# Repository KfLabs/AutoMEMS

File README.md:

MotionProcessing
================

Code for motion sensors

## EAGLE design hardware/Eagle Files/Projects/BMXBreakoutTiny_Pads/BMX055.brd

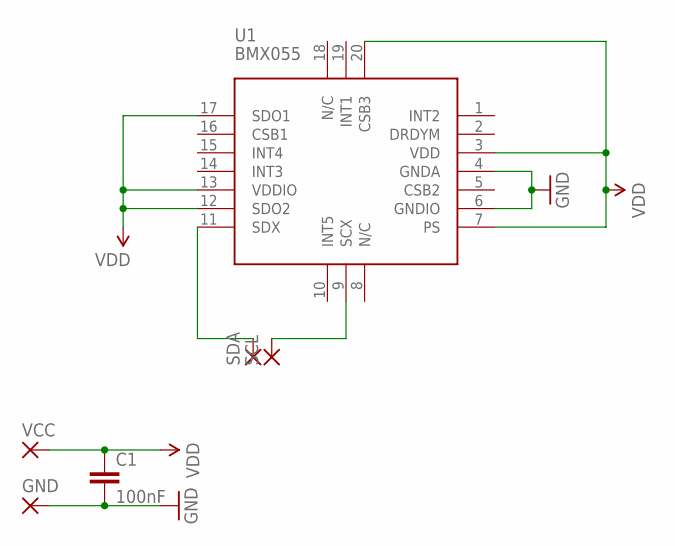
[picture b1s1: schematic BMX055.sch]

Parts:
C1: 100nF; 1206
GND: SMD2; SMD1,27-2,54
SCL: SMD2; SMD1,27-2,54
SDA: SMD2; SMD1,27-2,54
U1: BMX055
VCC: SMD2; SMD1,27-2,54

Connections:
GND: C1.2, GND.1, U1.4 (GNDA), U1.6 (GNDIO)
unnamed: SCL.1, U1.9 (SCX)
unnamed: SDA.1, U1.11 (SDX)
VDD: C1.1, U1.3 (VDD), U1.7 (PS), U1.12 (SDO2), U1.13 (VDDIO), U1.17 (SDO1), U1.20 (CSB3), VCC.1

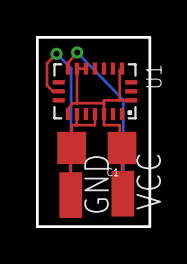
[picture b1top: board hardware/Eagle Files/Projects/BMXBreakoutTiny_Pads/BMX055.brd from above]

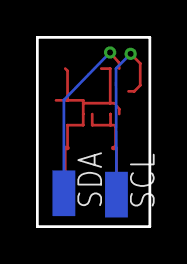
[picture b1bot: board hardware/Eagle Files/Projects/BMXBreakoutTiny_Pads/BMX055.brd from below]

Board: 2 copper layers, 6.2 x 10.5 mm, 6 parts (2 on the bottom side), 4 nets.

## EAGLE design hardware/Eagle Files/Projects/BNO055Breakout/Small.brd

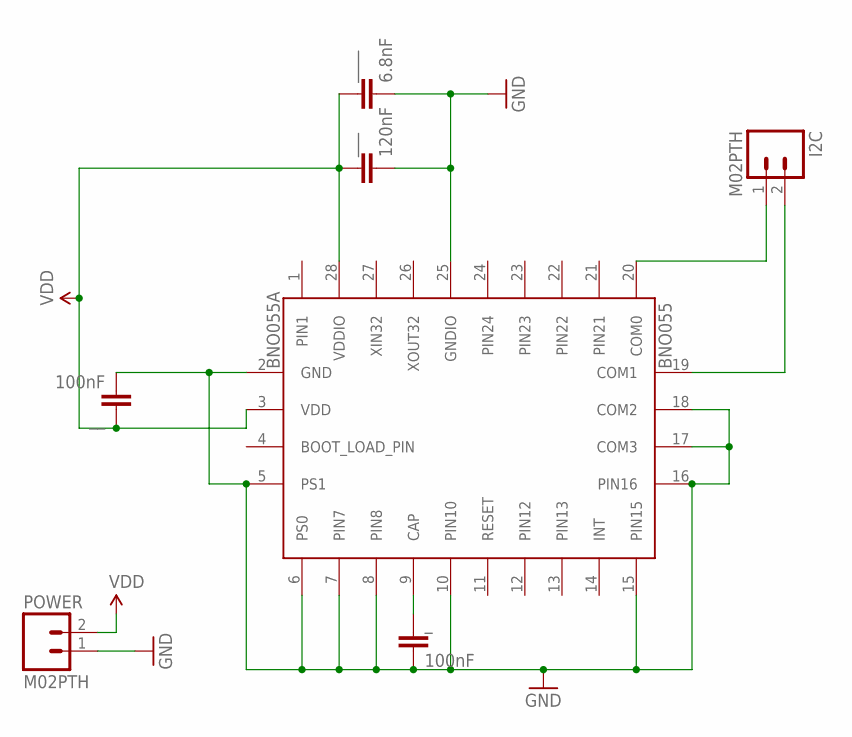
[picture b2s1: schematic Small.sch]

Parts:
BNO055: BNO055A; BNO055
I2C: M02PTH; 1X02
POWER: M02PTH; 1X02
_: 100nF; 1206
__: 100nF; 1206
___: 120nF; 1206
____: 6.8nF; 1206

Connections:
GND: BNO055.2 (GND), BNO055.5 (PS1), BNO055.6 (PS0), BNO055.7 (PIN7), BNO055.8 (PIN8), BNO055.10 (PIN10), BNO055.15 (PIN15), BNO055.16 (PIN16), BNO055.17 (COM3), BNO055.18 (COM2), BNO055.25 (GNDIO), POWER.1, _.2, __.2, ___.2, ____.2
unnamed: BNO055.9 (CAP), _.1
SCL: BNO055.19 (COM1), I2C.2
SDA: BNO055.20 (COM0), I2C.1
VDD: BNO055.3 (VDD), BNO055.28 (VDDIO), POWER.2, __.1, ___.1, ____.1

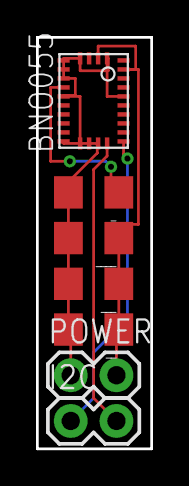
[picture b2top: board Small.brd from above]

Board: 2 copper layers, 6.3 x 22.9 mm, 7 parts (0 on the bottom side), 5 nets.

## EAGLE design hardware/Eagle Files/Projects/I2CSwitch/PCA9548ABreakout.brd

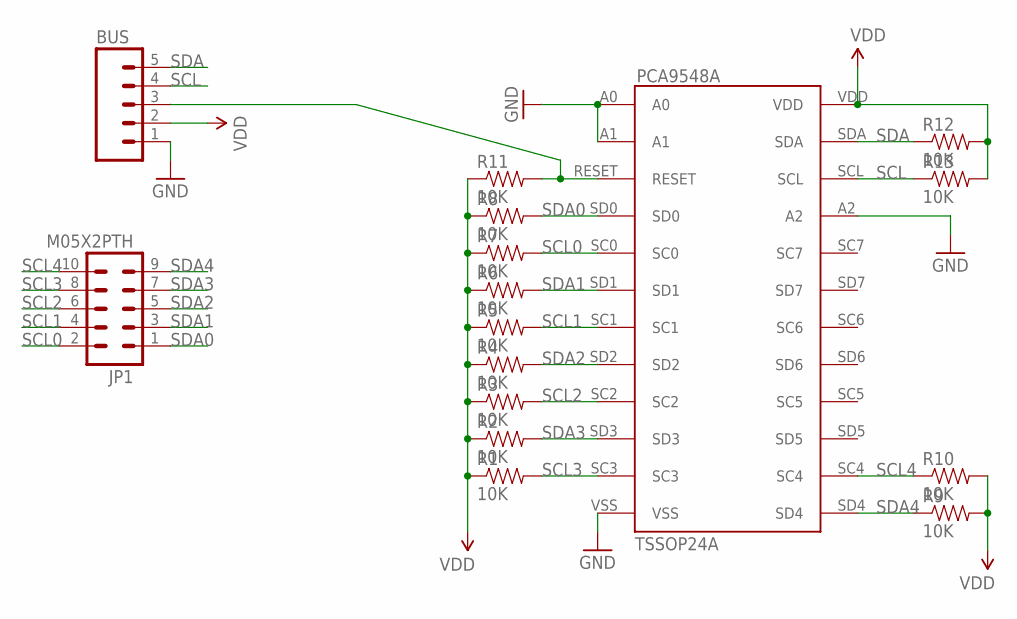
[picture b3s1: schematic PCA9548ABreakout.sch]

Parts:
BUS: M05PTH; 1X05
JP1: M05X2PTH; AVR_ICSP
PCA9548A: TSSOP24A; TSSOP24
R1, R2, R3, R4, R5, R6, R7, R8, R9, R10, R11, R12, R13: 10K; 0603-RES

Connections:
GND: BUS.1, PCA9548A.A0, PCA9548A.A1, PCA9548A.A2, PCA9548A.VSS
unnamed: BUS.3, PCA9548A.RESET, R11.2
SCL: BUS.4, PCA9548A.SCL, R13.1
SCL0: JP1.2, PCA9548A.SC0, R7.2
SCL1: JP1.4, PCA9548A.SC1, R5.2
SCL2: JP1.6, PCA9548A.SC2, R3.2
SCL3: JP1.8, PCA9548A.SC3, R1.2
SCL4: JP1.10, PCA9548A.SC4, R10.1
SDA: BUS.5, PCA9548A.SDA, R12.1
SDA0: JP1.1, PCA9548A.SD0, R8.2
SDA1: JP1.3, PCA9548A.SD1, R6.2
SDA2: JP1.5, PCA9548A.SD2, R4.2
SDA3: JP1.7, PCA9548A.SD3, R2.2
SDA4: JP1.9, PCA9548A.SD4, R9.1
VDD: BUS.2, PCA9548A.VDD, R1.1, R2.1, R3.1, R4.1, R5.1, R6.1, R7.1, R8.1, R9.2, R10.2, R11.1, R12.2, R13.2

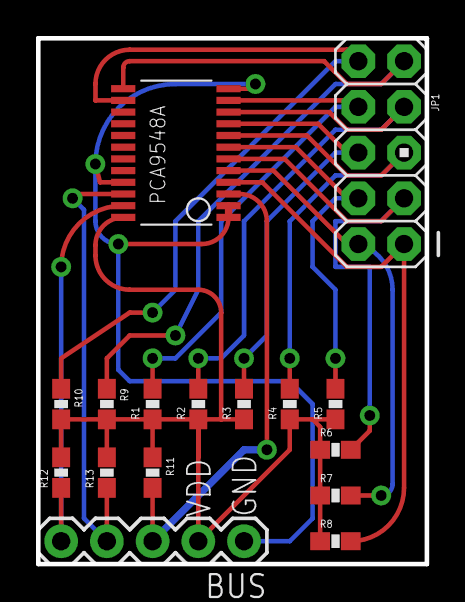
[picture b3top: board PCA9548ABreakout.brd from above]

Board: 2 copper layers, 21.6 x 29.2 mm, 16 parts (0 on the bottom side), 15 nets.

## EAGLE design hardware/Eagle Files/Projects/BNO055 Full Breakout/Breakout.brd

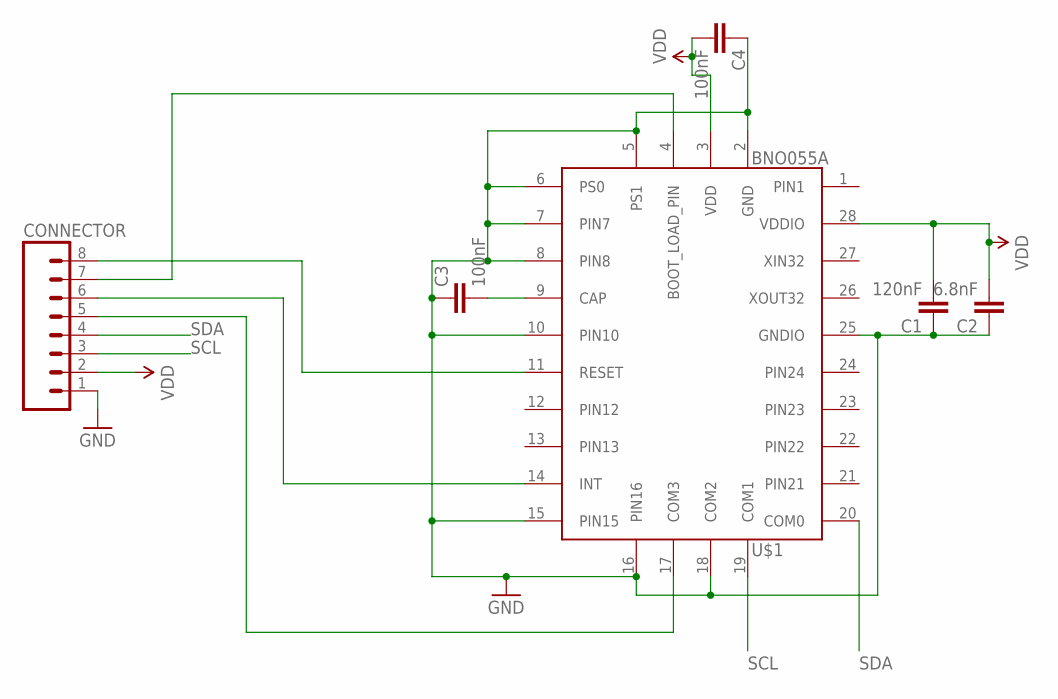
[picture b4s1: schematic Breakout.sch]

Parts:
C1: 120nF; 1206
C2: 6.8nF; 1206
C3, C4: 100nF; 1206
CONNECTOR: M08NO_SILK; 1X08_NO_SILK
U$1: BNO055A; BNO055

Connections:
GND: C1.1, C2.1, C3.1, C4.1, CONNECTOR.1, U$1.2 (GND), U$1.5 (PS1), U$1.6 (PS0), U$1.7 (PIN7), U$1.8 (PIN8), U$1.10 (PIN10), U$1.15 (PIN15), U$1.16 (PIN16), U$1.18 (COM2), U$1.25 (GNDIO)
unnamed: CONNECTOR.8, U$1.11 (RESET)
unnamed: C3.2, U$1.9 (CAP)
unnamed: CONNECTOR.7, U$1.4 (BOOT_LOAD_PIN)
unnamed: CONNECTOR.6, U$1.14 (INT)
unnamed: CONNECTOR.5, U$1.17 (COM3)
SCL: CONNECTOR.3, U$1.19 (COM1)
SDA: CONNECTOR.4, U$1.20 (COM0)
VDD: C1.2, C2.2, C4.2, CONNECTOR.2, U$1.3 (VDD), U$1.28 (VDDIO)

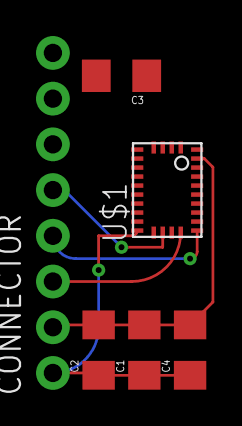
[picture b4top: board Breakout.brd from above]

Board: 2 copper layers, 6 parts (0 on the bottom side), 9 nets.

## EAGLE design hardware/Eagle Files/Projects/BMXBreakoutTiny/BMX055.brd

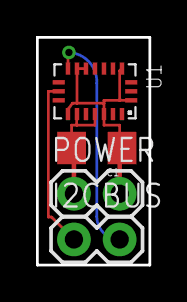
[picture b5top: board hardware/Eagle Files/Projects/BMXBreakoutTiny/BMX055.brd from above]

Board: 2 copper layers, 6.2 x 12.6 mm, 4 parts (0 on the bottom side), 4 nets.

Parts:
C1: 100nF; 1206
I2CBUS: M02PTH; 1X02
POWER: M02PTH; 1X02
U1: BMX055

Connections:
GND: C1.2, POWER.1, U1.4, U1.6
unnamed: I2CBUS.1, U1.9
unnamed: I2CBUS.2, U1.11
VDD: C1.1, POWER.2, U1.3, U1.7, U1.12, U1.13, U1.17, U1.20

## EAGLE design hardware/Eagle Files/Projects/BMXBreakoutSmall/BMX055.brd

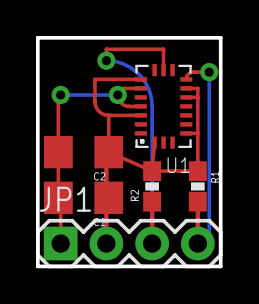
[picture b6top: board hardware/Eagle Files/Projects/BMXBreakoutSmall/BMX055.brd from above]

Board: 2 copper layers, 10.2 x 12.7 mm, 7 parts (0 on the bottom side), 4 nets.

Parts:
C1, C2: 100nF; 1206
FRAME1: FRAME-LETTER; CREATIVE_COMMONS
JP1: 1X04
R1, R2: 10K; 0603-RES
U1: BMX055

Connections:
GND: C1.2, C2.2, JP1.1, U1.4, U1.6
unnamed: JP1.3, R2.1, U1.9
unnamed: JP1.4, R1.2, U1.11
VDD: C1.1, C2.1, JP1.2, R1.1, R2.2, U1.3, U1.7, U1.12, U1.13, U1.17, U1.20

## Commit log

2014-10-15 Initial placement of current code & files
2014-10-15 Moved Francesco's cost breakdown

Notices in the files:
parts and their libraries:
SparkFun-Aesthetics: Licensing: Creative Commons ShareAlike 4.0 International - https://creativecommons.org/licenses/by-sa/4.0
SparkFun-Aesthetics: Released under the Creative Commons Attribution Share-Alike 4.0 License
SparkFun-Aesthetics: https://creativecommons.org/licenses/by-sa/4.0
